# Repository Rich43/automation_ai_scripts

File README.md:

# Automation AI Scripts

Collection of experimental automation utilities and demos.

This repository began as **automation-scripts**, a small prototype for
desktop automation. Another AI agent expanded the project into a more
comprehensive solution called **AutomationToolkit**, which now lives in its
own directory alongside the original scripts.

## 🖥 Setup Instructions

Run the setup script for your operating system:

**Linux:**
```bash
chmod +x setup_linux.sh
./setup_linux.sh
```

**macOS:**
```bash
chmod +x setup_mac.sh
./setup_mac.sh
```

**Windows (PowerShell):**
```powershell
.\setup_windows.ps1
```

After installation:
```bash
poetry shell
```

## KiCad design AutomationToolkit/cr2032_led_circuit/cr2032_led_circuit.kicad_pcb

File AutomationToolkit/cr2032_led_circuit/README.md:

# Cr2032 Led Circuit

## Circuit Description
Simple LED circuit powered by CR2032 battery with push button switch.

## Components:
- BT1: CR2032 3V Lithium Battery
- SW1: Momentary Push Button Switch  
- D1: LED (any color)
- R1: 330Ω Current Limiting Resistor

## Circuit Operation:
When the push button (SW1) is pressed, current flows from the positive terminal of the CR2032 battery (BT1) through the 330Ω resistor (R1), through the LED (D1), and back to the negative terminal of the battery, completing the circuit and lighting the LED.

## Files Generated:
- cr2032_led_circuit.sch: KiCad schematic file
- cr2032_led_circuit.kicad_pcb: KiCad PCB layout file  
- cr2032_led_circuit.pro: KiCad project file

## Created: 2025-07-22 00:22:16

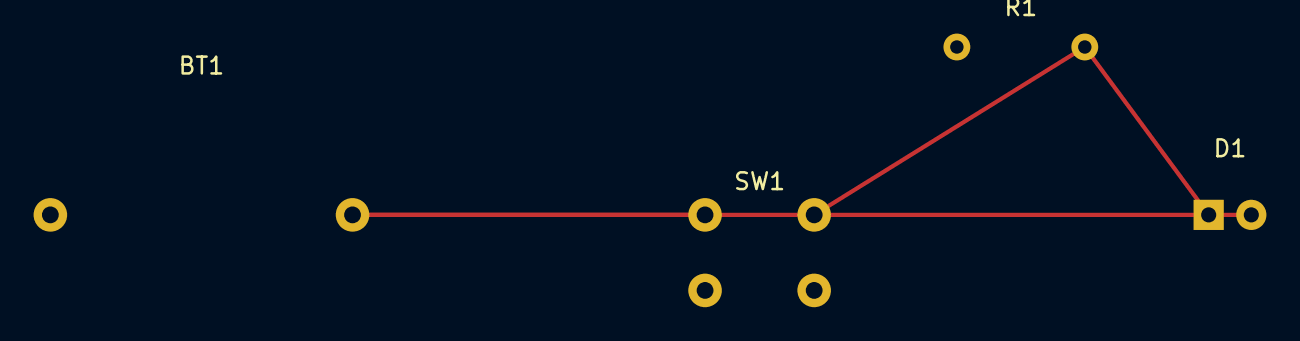
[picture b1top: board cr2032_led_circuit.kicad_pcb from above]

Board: 2 copper layers, 4 parts (0 on the bottom side), 2 nets.

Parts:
BT1: CR2032; BatteryHolder_Keystone_3000_1x12mm
D1: LED; LED_D5.0mm
R1: 330R; R_Axial_DIN0207_L6.3mm_D2.5mm_P7.62mm_Horizontal
SW1: SW_Push; SW_PUSH_6mm

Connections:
+BATT: BT1.1, D1.1, R1.1, R1.2, SW1.1, SW1.2, SW1.3, SW1.4
GND: BT1.2, D1.2

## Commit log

2025-07-22 Update deployment guide install instructions
2025-07-22 docs: update API key setup instructions
2025-07-22 docs: add project guidelines
2025-07-22 docs: add setup instructions
2025-07-22 docs: clarify project evolution in README
2025-07-22 docs: add unit testing plan
2025-07-22 test: expand coverage
2025-07-22 ci: add GitHub workflow for unit tests
2025-07-22 test: expand utils coverage
